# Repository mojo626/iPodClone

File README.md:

# iPodClone

This is a clone of an iPod video based on the Allwinner V3s processor

Features include:
- Allwinner V3s processor
- 1.54" TFT LCD
- ESP32 for WiFi and Bluetooth
- STGL5000 for wired headphone output
- 2500mAh battery
- microSD for music storage and filesystem
- NAND flash for boot

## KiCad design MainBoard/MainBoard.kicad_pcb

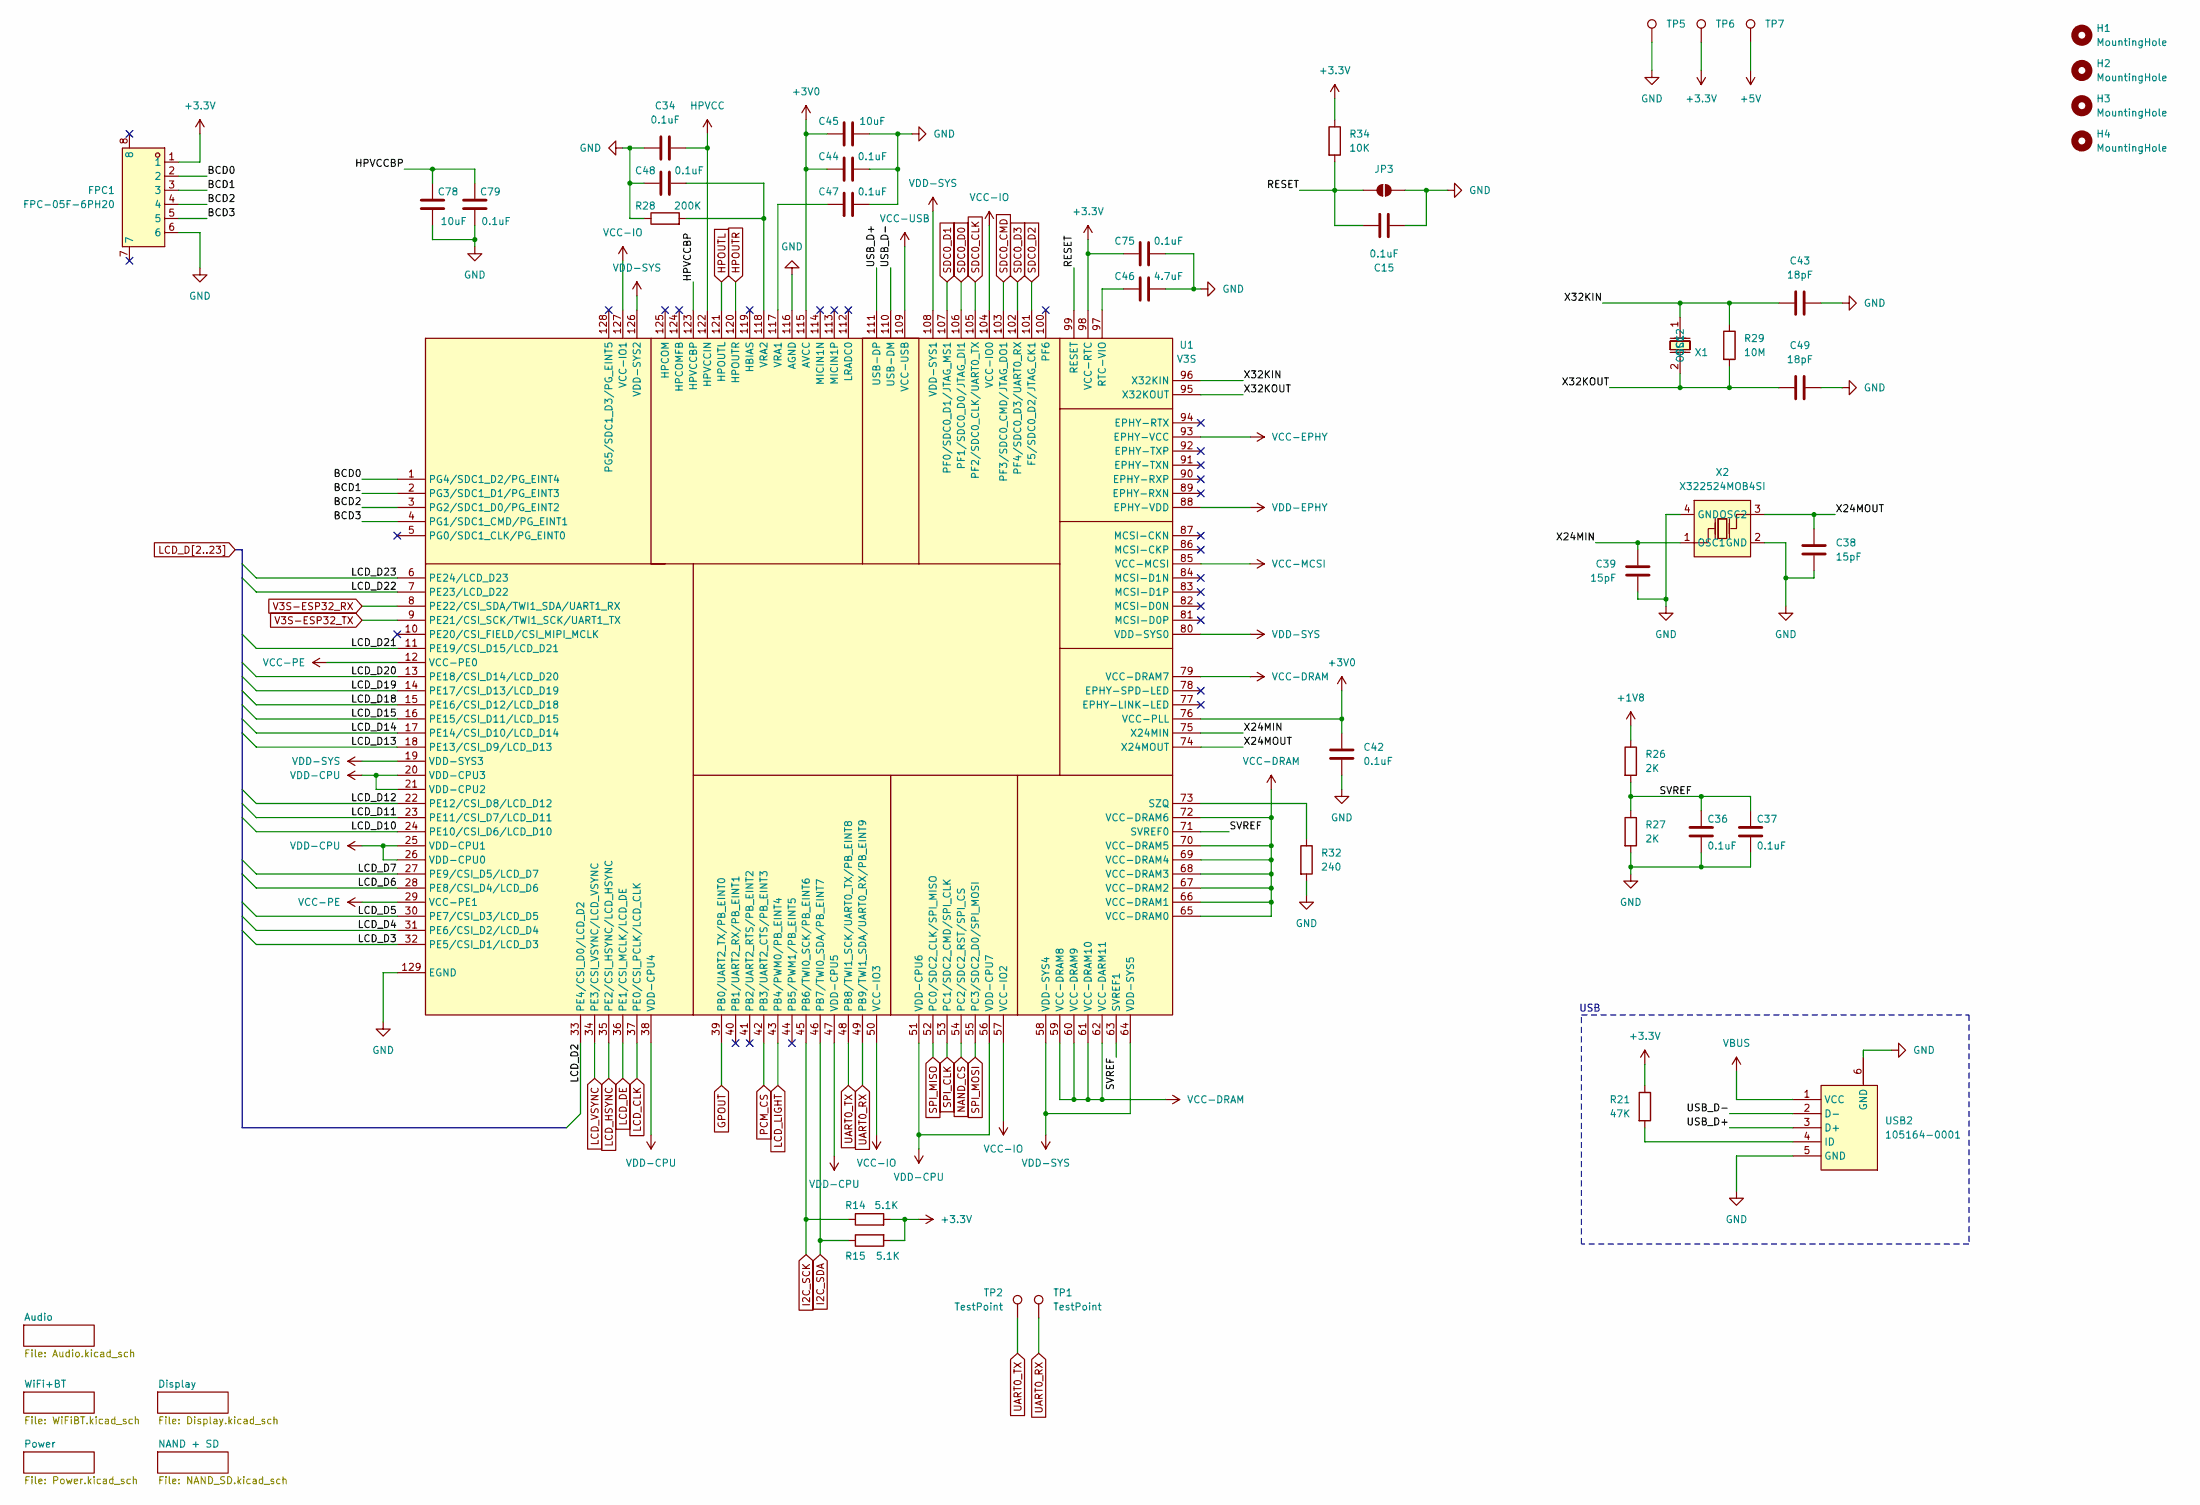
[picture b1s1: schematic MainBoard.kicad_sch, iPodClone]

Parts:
C15, C34, C36, C37, C42, C44, C47, C48, C75, C79: 0.1uF; C_0402_1005Metric
C38, C39: 15pF; C_0402_1005Metric
C43, C49: 18pF; C_0402_1005Metric
C45, C78: 10uF; C_0603_1608Metric
C46: 4.7uF; C_0402_1005Metric
FPC1: FPC-05F-6PH20; FPC-SMD_6P-P0.50_XUNPU_FPC-05F-6PH20; LCSC Part C2856796
H1, H2, H3, H4: MountingHole; MountingHole_2.2mm_M2
JP3: SolderJumper_2_Open; SolderJumper-2_P1.3mm_Open_Pad1.0x1.5mm
R14, R15: 5.1K; R_0402_1005Metric
R21: 47K; R_0402_1005Metric
R26, R27: 2K; R_0402_1005Metric
R28: 200K; R_0402_1005Metric
R29: 10M; R_0402_1005Metric
R32: 240; R_0402_1005Metric
R34: 10K; R_0402_1005Metric
TP1, TP2, TP5, TP6, TP7: TestPoint; TestPoint_Pad_1.5x1.5mm
U1: V3S; LQFP-128_L14.0-W14.0-P0.40-LS16.0-BL-EP5.0; LCSC Part C2687449
USB2: 105164-0001; MICRO-USB-SMD_5P-P0.65-H-F_105164-0001; LCSC Part C234179
X1: FC-12M32.768KHZ7PF20PPM; FC-12M_L2.0-W1.2; LCSC Part C99009
X2: X322524MOB4SI; CRYSTAL-SMD_4P-L3.2-W2.5-BL; LCSC Part C70590

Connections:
+1V2: U1.19 (VDD-SYS3), U1.20 (VDD-CPU3), U1.21 (VDD-CPU2), U1.25 (VDD-CPU1), U1.26 (VDD-CPU0), U1.38 (VDD-CPU4), U1.47 (VDD-CPU5), U1.51 (VDD-CPU6), U1.56 (VDD-CPU7), U1.58 (VDD-SYS4), U1.64 (VDD-SYS5), U1.80 (VDD-SYS0), U1.88 (EPHY-VDD), U1.108 (VDD-SYS1), U1.126 (VDD-SYS2); also elsewhere on the board
+1V8: R26.1, U1.59 (VCC-DRAM8), U1.60 (VCC-DRAM9), U1.61 (VCC-DRAM10), U1.62 (VCC-DARM11), U1.65 (VCC-DRAM0), U1.66 (VCC-DRAM1), U1.67 (VCC-DRAM2), U1.68 (VCC-DRAM3), U1.69 (VCC-DRAM4), U1.70 (VCC-DRAM5), U1.72 (VCC-DRAM6), U1.79 (VCC-DRAM7); also elsewhere on the board
+3.3V: C34.1, C75.2, FPC1.1, R14.2, R15.2, R21.1, R34.1, TP6.1, U1.12 (VCC-PE0), U1.29 (VCC-PE1), U1.50 (VCC-IO3), U1.57 (VCC-IO2), U1.85 (VCC-MCSI), U1.93 (EPHY-VCC), U1.98 (VCC-RTC), U1.104 (VCC-IO0), U1.109 (VCC-USB), U1.122 (HPVCCIN), U1.127 (VCC-IO1); also elsewhere on the board
+3V0: C42.1, C44.2, C45.2, U1.76 (VCC-PLL), U1.115 (AVCC); also elsewhere on the board
+5V: TP7.1; also elsewhere on the board
/BCD0: FPC1.2, U1.1 (PG4/SDC1_D2/PG_EINT4)
/BCD1: FPC1.3, U1.2 (PG3/SDC1_D1/PG_EINT3)
/BCD2: FPC1.4, U1.3 (PG2/SDC1_D0/PG_EINT2)
/BCD3: FPC1.5, U1.4 (PG1/SDC1_CMD/PG_EINT1)
/HPVCCBP: C78.2, C79.2, U1.123 (HPVCCBP)
/RESET: C15.1, JP3.2 (B), R34.2, U1.99 (RESET)
/SVREF: C36.1, C37.1, R26.2, R27.1, U1.63 (SVREF1), U1.71 (SVREF0)
/USB_D+: U1.111 (USB-DP), USB2.3 (D+)
/USB_D-: U1.110 (USB-DM), USB2.2 (D-)
/X24MIN: C39.1, U1.75 (X24MIN), X2.1 (OSC1)
/X24MOUT: C38.1, U1.74 (X24MOUT), X2.3 (OSC2)
/X32KIN: C43.1, R29.1, U1.96 (X32KIN), X1.1 (OSC1)
/X32KOUT: C49.1, R29.2, U1.95 (X32KOUT), X1.2 (OSC2)
GND: C15.2, C34.2, C36.2, C37.2, C38.2, C39.2, C42.2, C43.2, C44.1, C45.1, C46.1, C47.1, C48.2, C49.2, C75.1, C78.1, C79.1, FPC1.6, JP3.1 (A), R27.2, R28.1, R32.2, TP5.1, U1.116 (AGND), U1.129 (EGND), USB2.5 (GND), USB2.6 (GND), X2.2 (GND), X2.4 (GND); also elsewhere on the board
GPOUT: U1.39 (PB0/UART2_TX/PB_EINT0); also elsewhere on the board
HPOUTL: U1.121 (HPOUTL); also elsewhere on the board
HPOUTR: U1.120 (HPOUTR); also elsewhere on the board
I2C_SCK: R14.1, U1.45 (PB6/TWI0_SCK/PB_EINT6); also elsewhere on the board
I2C_SDA: R15.1, U1.46 (PB7/TWI0_SDA/PB_EINT7); also elsewhere on the board
LCD_CLK: U1.37 (PE0/CSI_PCLK/LCD_CLK); also elsewhere on the board
LCD_D2: U1.33 (PE4/CSI_D0/LCD_D2); also elsewhere on the board
LCD_D3: U1.32 (PE5/CSI_D1/LCD_D3); also elsewhere on the board
LCD_D4: U1.31 (PE6/CSI_D2/LCD_D4); also elsewhere on the board
LCD_D5: U1.30 (PE7/CSI_D3/LCD_D5); also elsewhere on the board
LCD_D6: U1.28 (PE8/CSI_D4/LCD_D6); also elsewhere on the board
LCD_D7: U1.27 (PE9/CSI_D5/LCD_D7); also elsewhere on the board
LCD_D10: U1.24 (PE10/CSI_D6/LCD_D10); also elsewhere on the board
LCD_D11: U1.23 (PE11/CSI_D7/LCD_D11); also elsewhere on the board
LCD_D12: U1.22 (PE12/CSI_D8/LCD_D12); also elsewhere on the board
LCD_D13: U1.18 (PE13/CSI_D9/LCD_D13); also elsewhere on the board
LCD_D14: U1.17 (PE14/CSI_D10/LCD_D14); also elsewhere on the board
LCD_D15: U1.16 (PE15/CSI_D11/LCD_D15); also elsewhere on the board
LCD_D18: U1.15 (PE16/CSI_D12/LCD_D18); also elsewhere on the board
LCD_D19: U1.14 (PE17/CSI_D13/LCD_D19); also elsewhere on the board
LCD_D20: U1.13 (PE18/CSI_D14/LCD_D20); also elsewhere on the board
LCD_D21: U1.11 (PE19/CSI_D15/LCD_D21); also elsewhere on the board
LCD_D22: U1.7 (PE23/LCD_D22); also elsewhere on the board
LCD_D23: U1.6 (PE24/LCD_D23); also elsewhere on the board
LCD_DE: U1.36 (PE1/CSI_MCLK/LCD_DE); also elsewhere on the board
LCD_HSYNC: U1.35 (PE2/CSI_HSYNC/LCD_HSYNC); also elsewhere on the board
LCD_LIGHT: U1.43 (PB4/PWM0/PB_EINT4); also elsewhere on the board
LCD_VSYNC: U1.34 (PE3/CSI_VSYNC/LCD_VSYNC); also elsewhere on the board
NAND_CS: U1.54 (PC2/SDC2_RST/SPI_CS); also elsewhere on the board
unnamed: C46.2, U1.97 (RTC-VIO)
unnamed: R32.1, U1.73 (SZQ)
unnamed: C47.2, U1.117 (VRA1)
unnamed: C48.1, R28.2, U1.118 (VRA2)
unnamed: R21.2, USB2.4 (ID)
PCM_CS: U1.42 (PB3/UART2_CTS/PB_EINT3); also elsewhere on the board
SDC0_CLK: U1.105 (PF2/SDC0_CLK/UART0_TX); also elsewhere on the board
SDC0_CMD: U1.103 (PF3/SDC0_CMD/JTAG_DO1); also elsewhere on the board
SDC0_D0: U1.106 (PF1/SDC0_D0/JTAG_DI1); also elsewhere on the board
SDC0_D1: U1.107 (PF0/SDC0_D1/JTAG_MS1); also elsewhere on the board
SDC0_D2: U1.101 (F5/SDC0_D2/JTAG_CK1); also elsewhere on the board
SDC0_D3: U1.102 (PF4/SDC0_D3/UART0_RX); also elsewhere on the board
SPI_CLK: U1.53 (PC1/SDC2_CMD/SPI_CLK); also elsewhere on the board
SPI_MISO: U1.52 (PC0/SDC2_CLK/SPI_MISO); also elsewhere on the board
SPI_MOSI: U1.55 (PC3/SDC2_D0/SPI_MOSI); also elsewhere on the board
UART0_RX: TP1.1, U1.49 (PB9/TWI1_SDA/UART0_RX/PB_EINT9)
UART0_TX: TP2.1, U1.48 (PB8/TWI1_SCK/UART0_TX/PB_EINT8)
V3S-ESP32_RX: U1.8 (PE22/CSI_SDA/TWI1_SDA/UART1_RX); also elsewhere on the board
V3S-ESP32_TX: U1.9 (PE21/CSI_SCK/TWI1_SCK/UART1_TX); also elsewhere on the board
VBUS: USB2.1 (VCC); also elsewhere on the board

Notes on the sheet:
USB

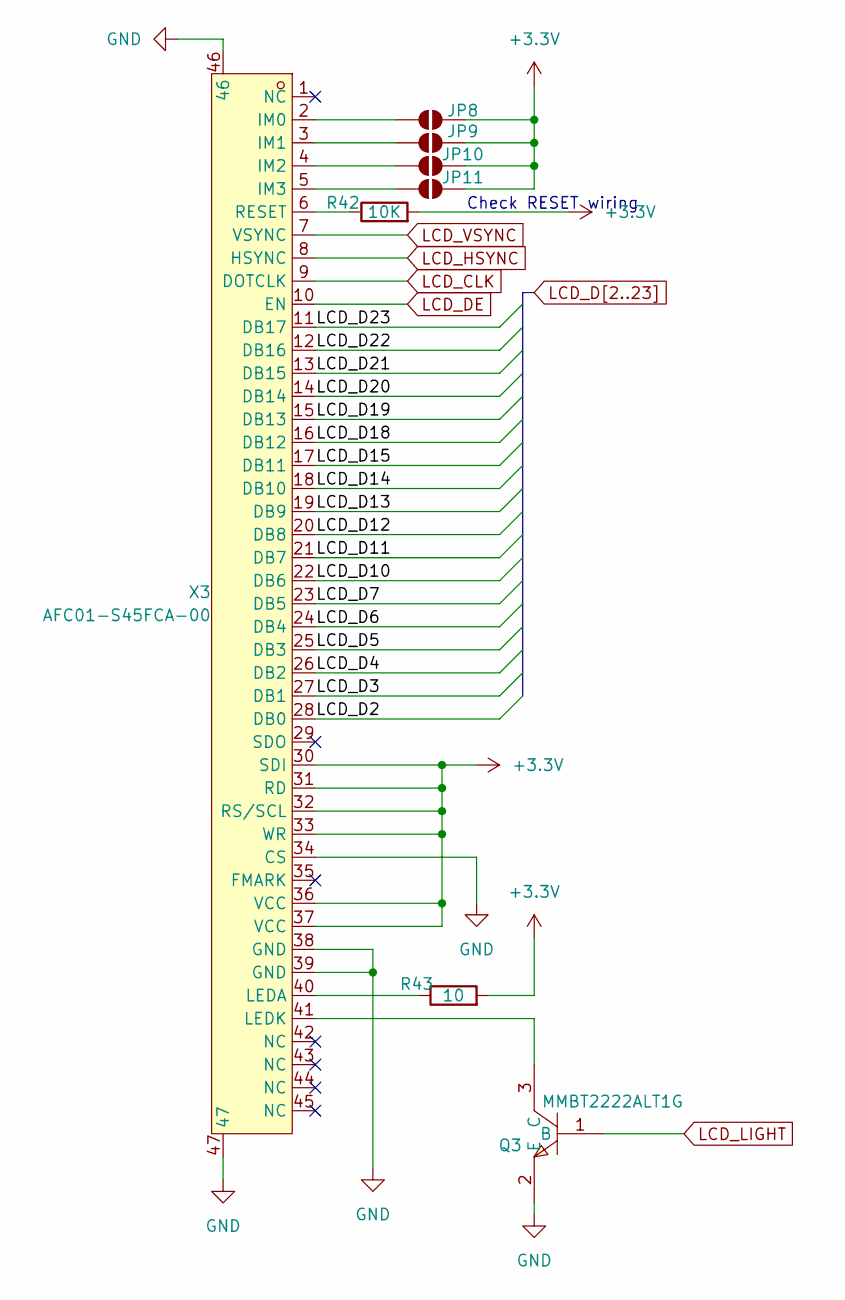
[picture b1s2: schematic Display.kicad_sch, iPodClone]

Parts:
JP8, JP9, JP10, JP11: SolderJumper_2_Open; SolderJumper-2_P1.3mm_Open_TrianglePad1.0x1.5mm
Q3: MMBT2222ALT1G; SOT-23-3_L2.9-W1.3-P1.90-LS2.4-BR; LCSC Part C82460
R42: 10K; R_0402_1005Metric
R43: 10; R_0402_1005Metric
X3: AFC01-S45FCA-00; FPC-SMD_AFC01-S45FCA-00; LCSC Part C262675

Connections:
+3.3V: JP8.2 (B), JP9.2 (B), JP10.2 (B), JP11.2 (B), R42.2, R43.2, X3.30 (SDI), X3.31 (RD), X3.32 (RS/SCL), X3.33 (WR), X3.36 (VCC), X3.37 (VCC); also elsewhere on the board
GND: Q3.2 (E), X3.34 (CS), X3.38 (GND), X3.39 (GND), X3.46, X3.47; also elsewhere on the board
LCD_CLK: X3.9 (DOTCLK); also elsewhere on the board
LCD_D2: X3.28 (DB0); also elsewhere on the board
LCD_D3: X3.27 (DB1); also elsewhere on the board
LCD_D4: X3.26 (DB2); also elsewhere on the board
LCD_D5: X3.25 (DB3); also elsewhere on the board
LCD_D6: X3.24 (DB4); also elsewhere on the board
LCD_D7: X3.23 (DB5); also elsewhere on the board
LCD_D10: X3.22 (DB6); also elsewhere on the board
LCD_D11: X3.21 (DB7); also elsewhere on the board
LCD_D12: X3.20 (DB8); also elsewhere on the board
LCD_D13: X3.19 (DB9); also elsewhere on the board
LCD_D14: X3.18 (DB10); also elsewhere on the board
LCD_D15: X3.17 (DB11); also elsewhere on the board
LCD_D18: X3.16 (DB12); also elsewhere on the board
LCD_D19: X3.15 (DB13); also elsewhere on the board
LCD_D20: X3.14 (DB14); also elsewhere on the board
LCD_D21: X3.13 (DB15); also elsewhere on the board
LCD_D22: X3.12 (DB16); also elsewhere on the board
LCD_D23: X3.11 (DB17); also elsewhere on the board
LCD_DE: X3.10 (EN); also elsewhere on the board
LCD_HSYNC: X3.8 (HSYNC); also elsewhere on the board
LCD_LIGHT: Q3.1 (B); also elsewhere on the board
LCD_VSYNC: X3.7 (VSYNC); also elsewhere on the board
unnamed: JP8.1 (A), X3.2 (IM0)
unnamed: JP9.1 (A), X3.3 (IM1)
unnamed: JP10.1 (A), X3.4 (IM2)
unnamed: JP11.1 (A), X3.5 (IM3)
unnamed: Q3.3 (C), X3.41 (LEDK)
unnamed: R43.1, X3.40 (LEDA)
unnamed: R42.1, X3.6 (RESET)

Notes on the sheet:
Check RESET wiring

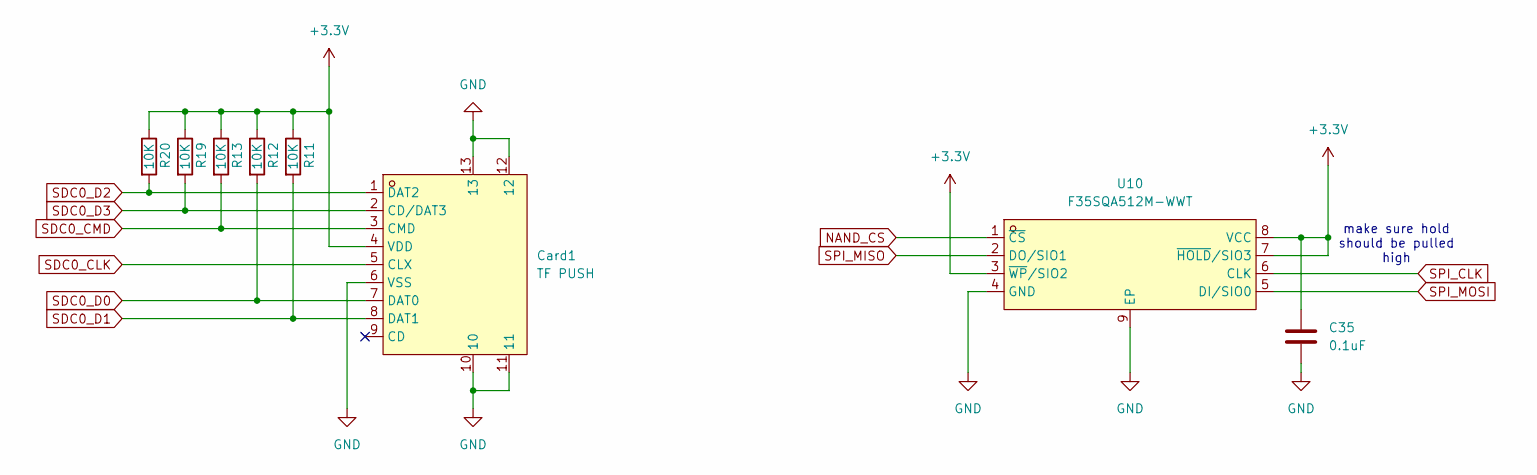
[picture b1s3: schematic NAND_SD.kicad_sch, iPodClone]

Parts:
C35: 0.1uF; C_0402_1005Metric
Card1: TF PUSH; TF-SMD_TF-PUSH; LCSC Part C393941
R11, R12, R13, R19, R20: 10K; R_0402_1005Metric
U10: F35SQA512M-WWT; WSON-8_L8.0-W6.0-P1.27-BL-EP-1; LCSC Part C5126826

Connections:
+3.3V: C35.1, Card1.4 (VDD), R11.1, R12.1, R13.1, R19.1, R20.1, U10.3 (~WP/SIO2), U10.7 (~HOLD/SIO3), U10.8 (VCC); also elsewhere on the board
GND: C35.2, Card1.6 (VSS), Card1.10, Card1.11, Card1.12, Card1.13, U10.4 (GND), U10.9 (EP); also elsewhere on the board
NAND_CS: U10.1 (~CS); also elsewhere on the board
SDC0_CLK: Card1.5 (CLX); also elsewhere on the board
SDC0_CMD: Card1.3 (CMD), R13.2; also elsewhere on the board
SDC0_D0: Card1.7 (DAT0), R12.2; also elsewhere on the board
SDC0_D1: Card1.8 (DAT1), R11.2; also elsewhere on the board
SDC0_D2: Card1.1 (DAT2), R20.2; also elsewhere on the board
SDC0_D3: Card1.2 (CD/DAT3), R19.2; also elsewhere on the board
SPI_CLK: U10.6 (CLK); also elsewhere on the board
SPI_MISO: U10.2 (DO/SIO1); also elsewhere on the board
SPI_MOSI: U10.5 (DI/SIO0); also elsewhere on the board

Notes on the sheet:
make sure hold should be pulled high

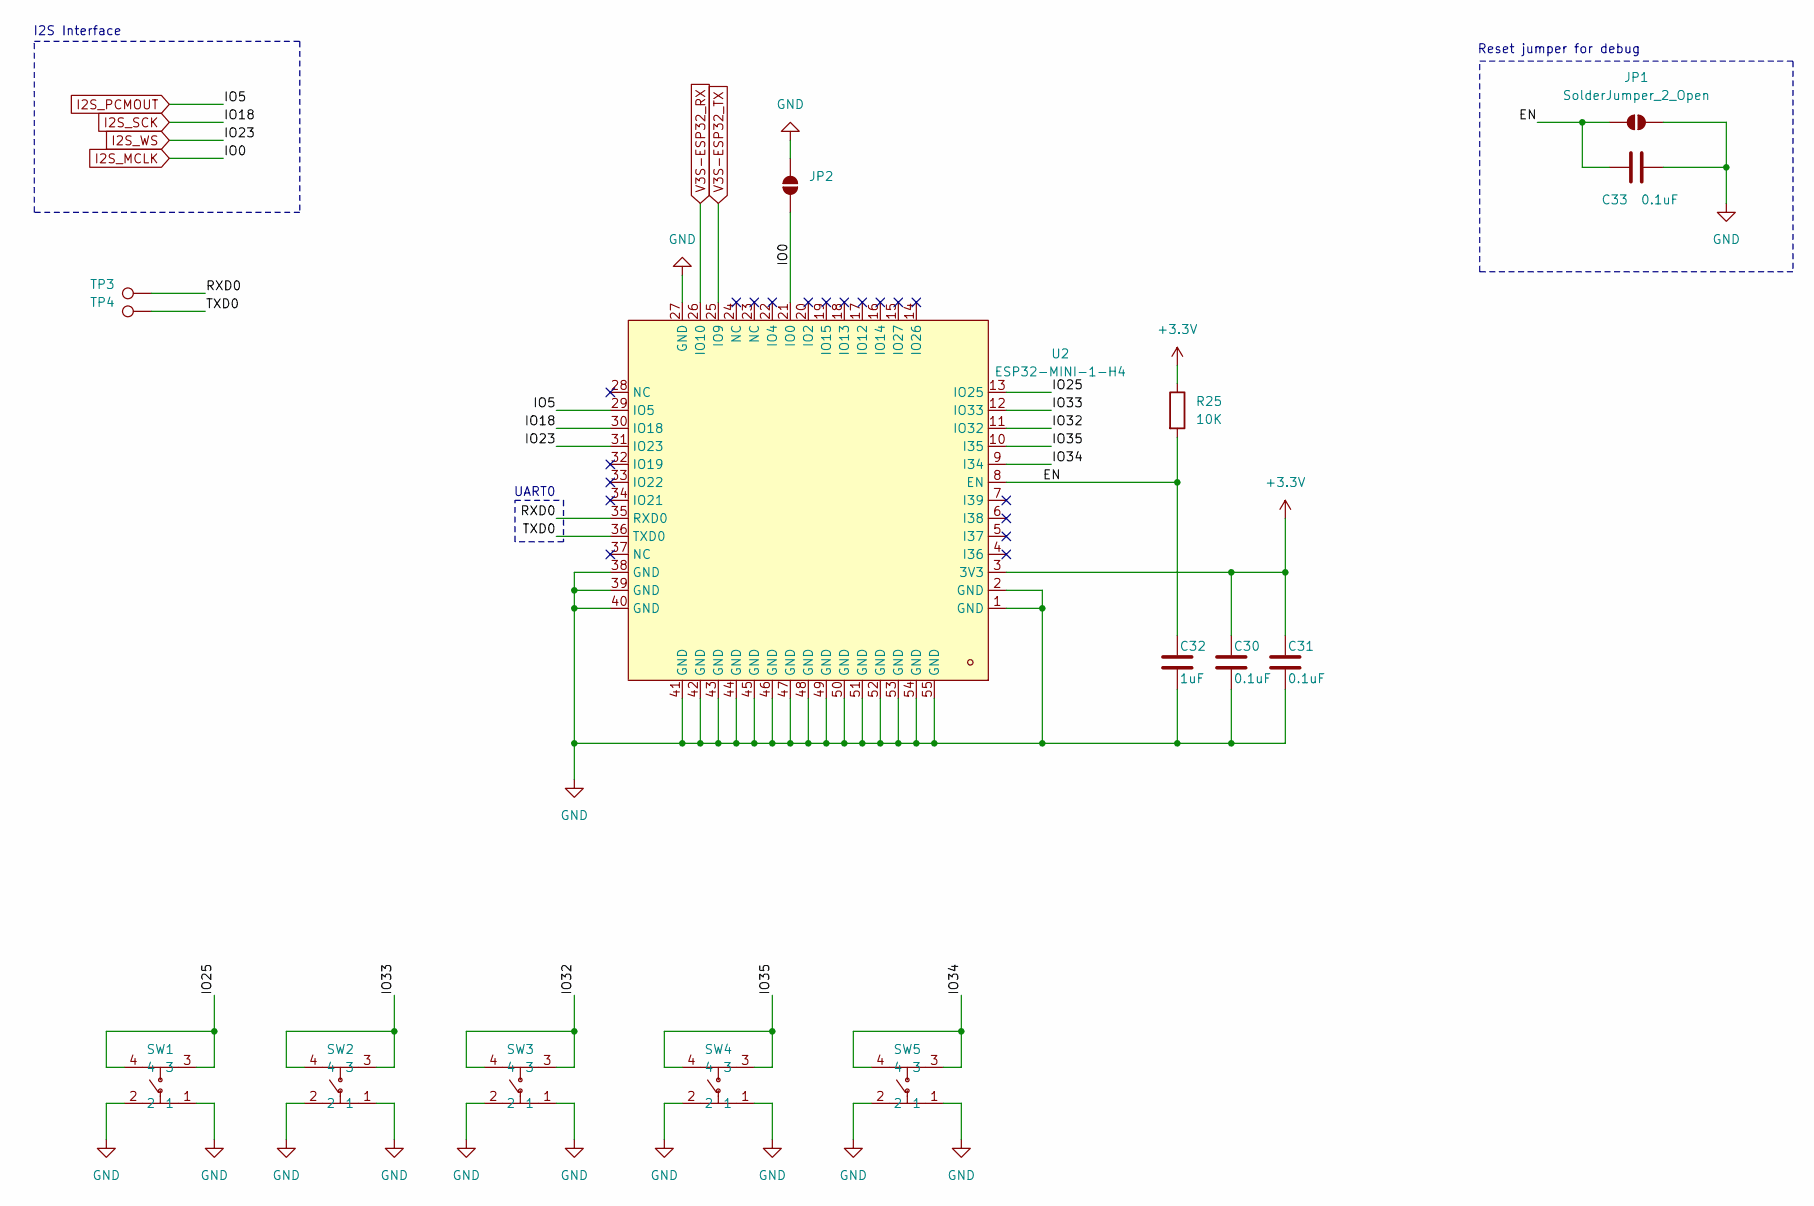
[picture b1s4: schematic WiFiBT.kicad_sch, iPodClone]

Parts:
C30, C31, C33: 0.1uF; C_0402_1005Metric
C32: 1uF; C_0402_1005Metric
JP1, JP2: SolderJumper_2_Open; SolderJumper-2_P1.3mm_Open_Pad1.0x1.5mm
R25: 10K; R_0402_1005Metric
SW1, SW2, SW3, SW4, SW5: TS3735A 250GF 030; SW-SMD_4P-L3.7-W3.7-P2.70-LS3.7; LCSC Part C2906282
TP3, TP4: TestPoint; TestPoint_Pad_1.5x1.5mm
U2: ESP32-MINI-1-H4; WIFI-SMD_ESP32-MINI-1; LCSC Part C3013933

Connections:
+3.3V: C30.1, C31.1, R25.1, U2.3 (3V3); also elsewhere on the board
/WiFi+BT/EN: C32.1, C33.1, JP1.1 (A), R25.2, U2.8 (EN)
/WiFi+BT/IO25: SW1.3, SW1.4, U2.13 (IO25)
/WiFi+BT/IO32: SW3.3, SW3.4, U2.11 (IO32)
/WiFi+BT/IO33: SW2.3, SW2.4, U2.12 (IO33)
/WiFi+BT/IO34: SW5.3, SW5.4, U2.9 (I34)
/WiFi+BT/IO35: SW4.3, SW4.4, U2.10 (I35)
/WiFi+BT/RXD0: TP3.1, U2.35 (RXD0)
/WiFi+BT/TXD0: TP4.1, U2.36 (TXD0)
GND: C30.2, C31.2, C32.2, C33.2, JP1.2 (B), JP2.2 (B), SW1.1, SW1.2, SW2.1, SW2.2, SW3.1, SW3.2, SW4.1, SW4.2, SW5.1, SW5.2, U2.1 (GND), U2.2 (GND), U2.27 (GND), U2.38 (GND), U2.39 (GND), U2.40 (GND), U2.41 (GND), U2.42 (GND), U2.43 (GND), U2.44 (GND), U2.45 (GND), U2.46 (GND), U2.47 (GND), U2.48 (GND), U2.49 (GND), U2.50 (GND), U2.51 (GND), U2.52 (GND), U2.53 (GND), U2.54 (GND), U2.55 (GND); also elsewhere on the board
I2S_MCLK: JP2.1 (A), U2.21 (IO0); also elsewhere on the board
I2S_PCMOUT: U2.29 (IO5); also elsewhere on the board
I2S_SCK: U2.30 (IO18); also elsewhere on the board
I2S_WS: U2.31 (IO23); also elsewhere on the board
V3S-ESP32_RX: U2.26 (IO10); also elsewhere on the board
V3S-ESP32_TX: U2.25 (IO9); also elsewhere on the board

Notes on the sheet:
UART0
I2S Interface
Reset jumper for debug

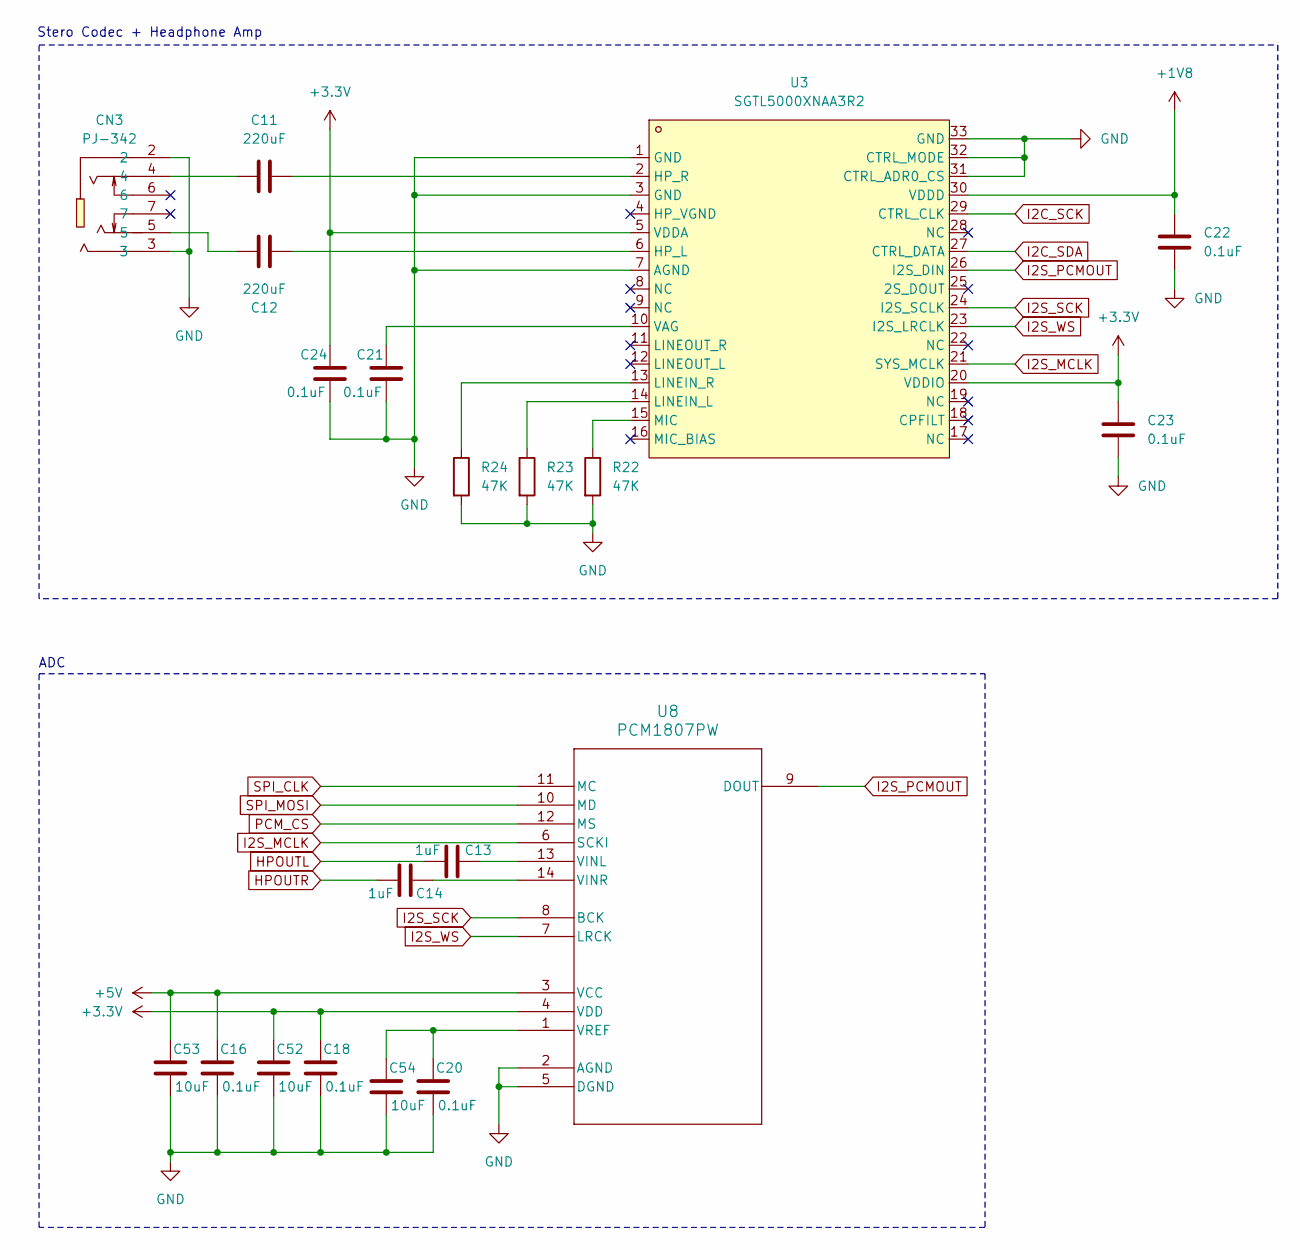
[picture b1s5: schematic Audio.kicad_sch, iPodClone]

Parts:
C11, C12: 220uF; C_1206_3216Metric
C13, C14: 1uF; C_0402_1005Metric
C16, C18, C20, C21, C22, C23, C24: 0.1uF; C_0402_1005Metric
C52, C53, C54: 10uF; C_0603_1608Metric
CN3: PJ-342; AUDIO-SMD_PJ-342; LCSC Part C668606
R22, R23, R24: 47K; R_0402_1005Metric
U3: SGTL5000XNAA3R2; QFN-32_L5.0-W5.0-P0.50-BL-EP3.4; LCSC Part C4991065
U8: PCM1807PW; PW14

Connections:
+1V8: C22.1, U3.30 (VDDD); also elsewhere on the board
+3.3V: C18.1, C23.1, C24.1, C52.1, U3.5 (VDDA), U3.20 (VDDIO), U8.4 (VDD); also elsewhere on the board
+5V: C16.1, C53.1, U8.3 (VCC); also elsewhere on the board
GND: C16.2, C18.2, C20.2, C21.2, C22.2, C23.2, C24.2, C52.2, C53.2, C54.2, CN3.2, CN3.3, R22.2, R23.2, R24.2, U3.1 (GND), U3.3 (GND), U3.7 (AGND), U3.31 (CTRL_ADR0_CS), U3.32 (CTRL_MODE), U3.33 (GND), U8.2 (AGND), U8.5 (DGND); also elsewhere on the board
HPOUTL: C13.1; also elsewhere on the board
HPOUTR: C14.1; also elsewhere on the board
I2C_SCK: U3.29 (CTRL_CLK); also elsewhere on the board
I2C_SDA: U3.27 (CTRL_DATA); also elsewhere on the board
I2S_MCLK: U3.21 (SYS_MCLK), U8.6 (SCKI); also elsewhere on the board
I2S_PCMOUT: U3.26 (I2S_DIN), U8.9 (DOUT); also elsewhere on the board
I2S_SCK: U3.24 (I2S_SCLK), U8.8 (BCK); also elsewhere on the board
I2S_WS: U3.23 (I2S_LRCLK), U8.7 (LRCK); also elsewhere on the board
unnamed: C11.1, CN3.4
unnamed: C12.1, CN3.5
unnamed: C12.2, U3.6 (HP_L)
unnamed: C11.2, U3.2 (HP_R)
unnamed: R23.1, U3.14 (LINEIN_L)
unnamed: R24.1, U3.13 (LINEIN_R)
unnamed: R22.1, U3.15 (MIC)
unnamed: C21.1, U3.10 (VAG)
unnamed: C13.2, U8.13 (VINL)
unnamed: C14.2, U8.14 (VINR)
unnamed: C20.1, C54.1, U8.1 (VREF)
PCM_CS: U8.12 (MS); also elsewhere on the board
SPI_CLK: U8.11 (MC); also elsewhere on the board
SPI_MOSI: U8.10 (MD); also elsewhere on the board

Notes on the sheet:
ADC
Stero Codec + Headphone Amp

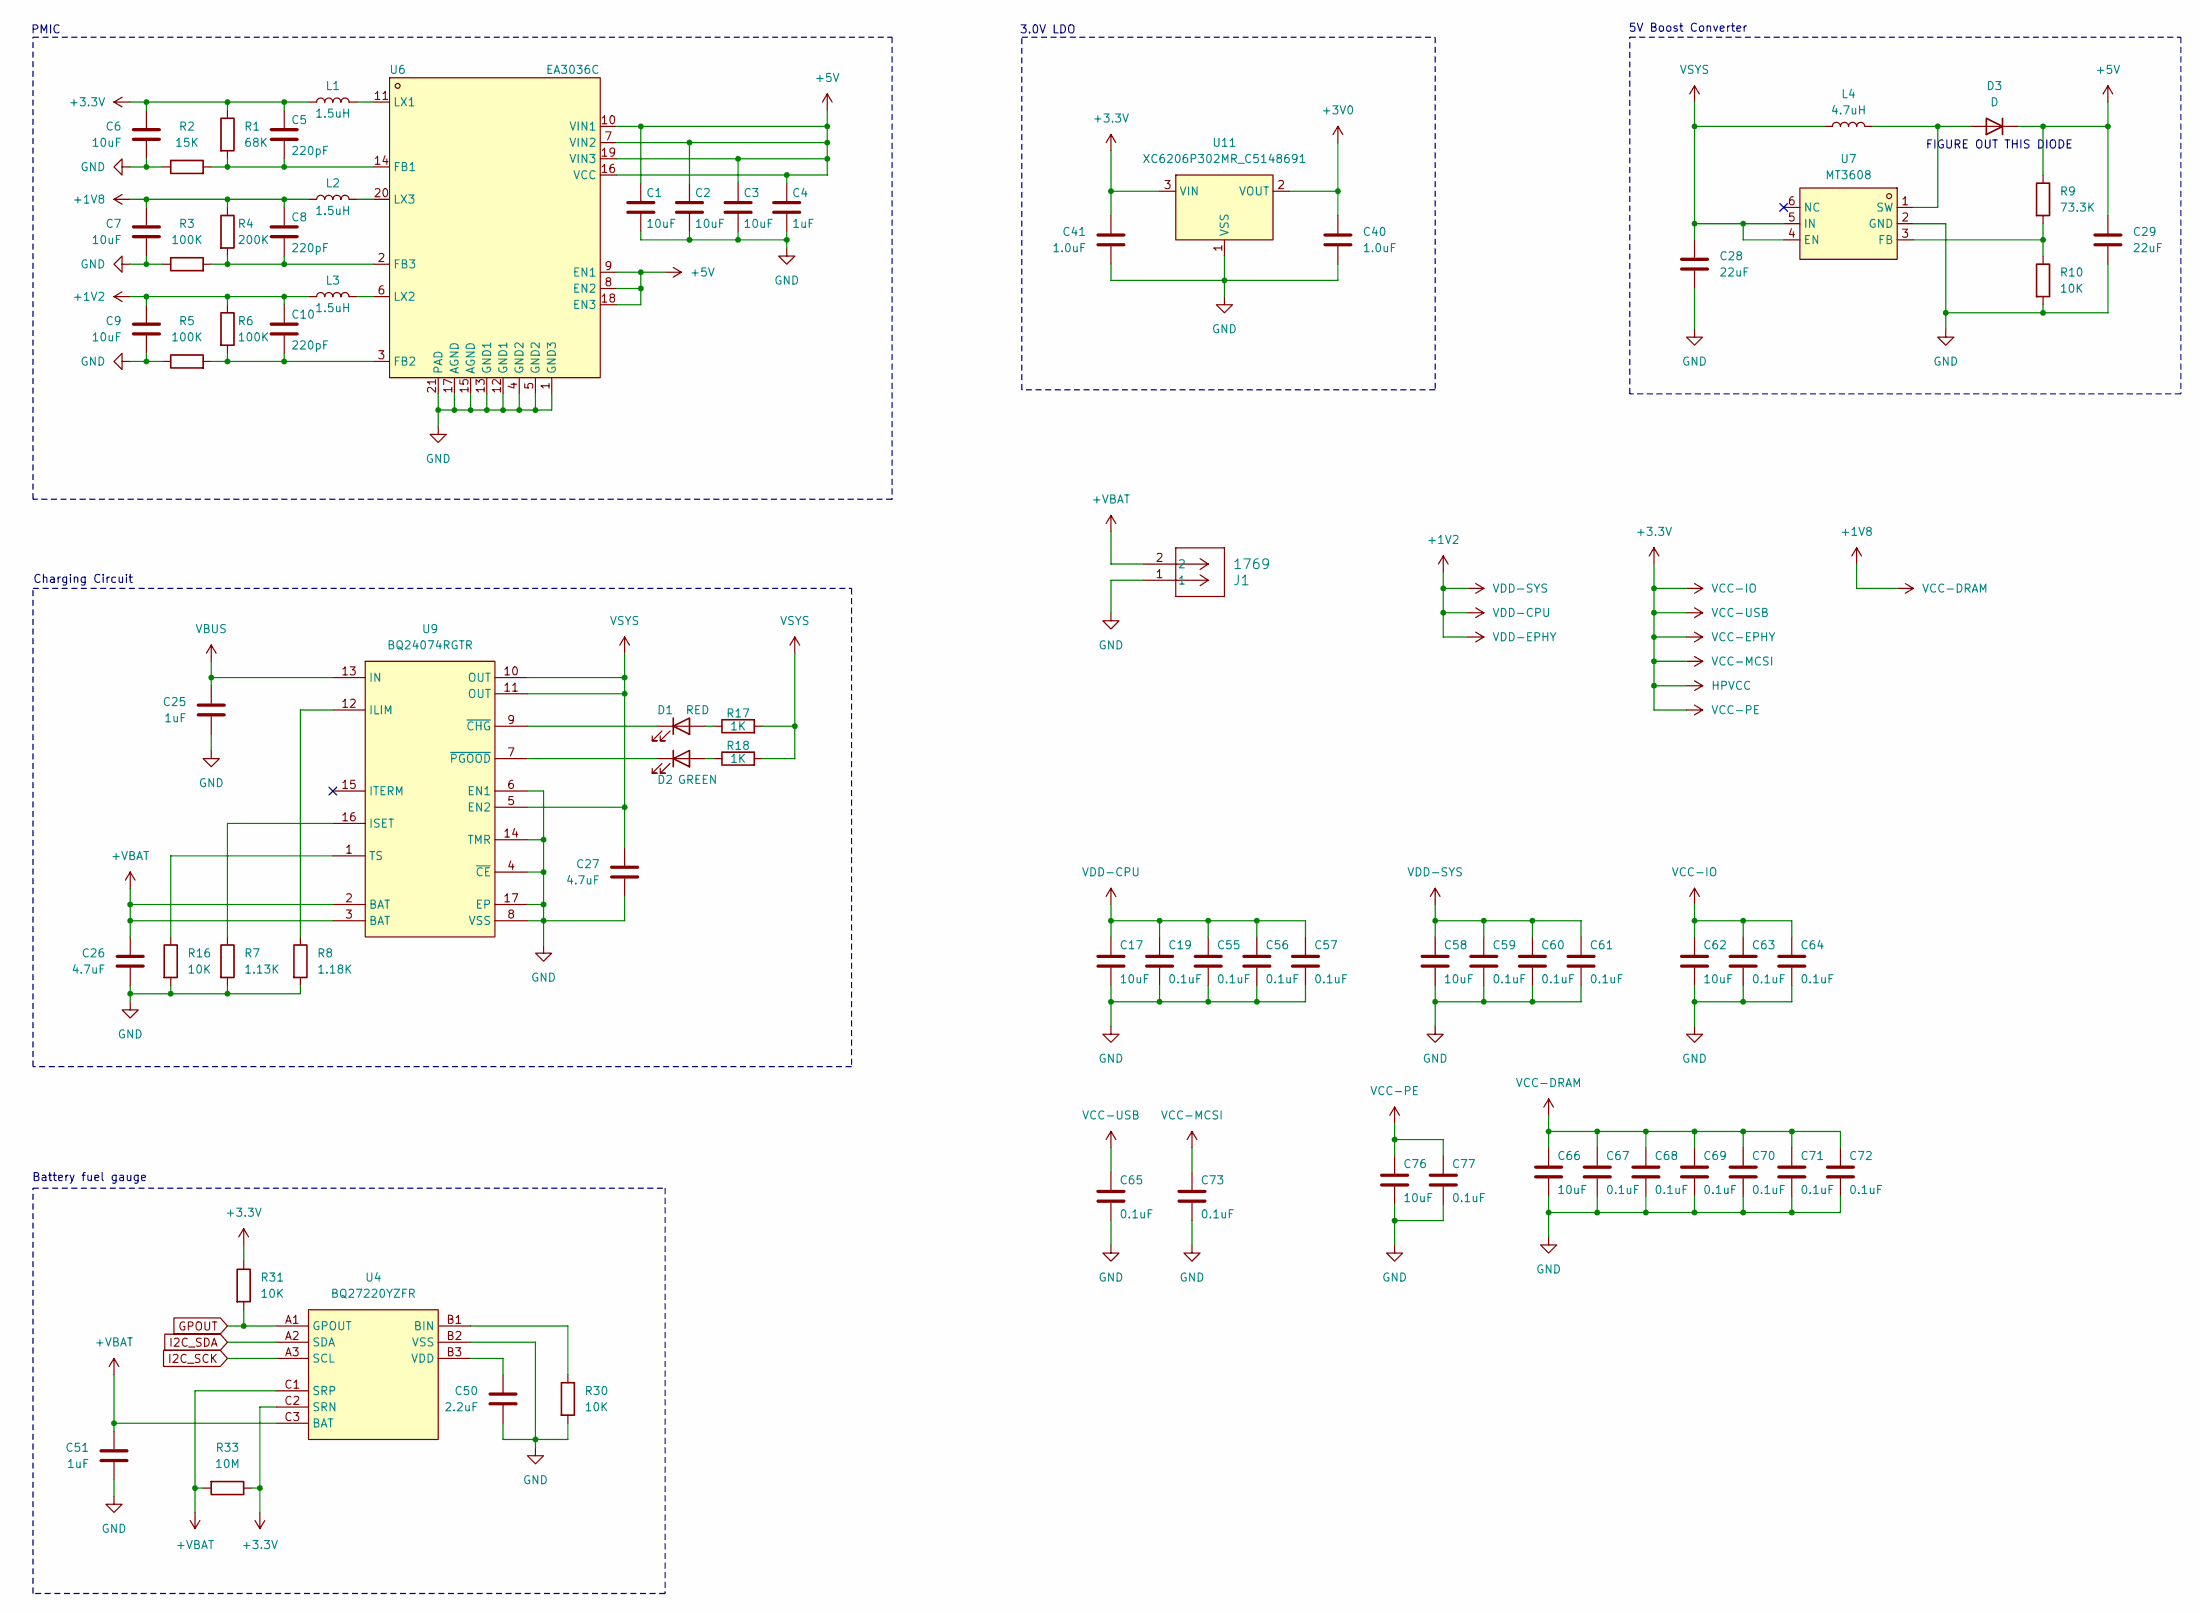
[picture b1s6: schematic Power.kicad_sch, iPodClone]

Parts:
C1, C2, C3, C6, C7, C9, C17, C58, C62, C66, C76: 10uF; C_0603_1608Metric
C4, C25, C51: 1uF; C_0402_1005Metric
C5, C8, C10: 220pF; C_0402_1005Metric
C19, C55, C56, C57, C59, C60, C61, C63, C64, C65, C67, C68, C69, C70, C71, C72, C73, C77: 0.1uF; C_0402_1005Metric
C26, C27: 4.7uF; C_0402_1005Metric
C28, C29: 22uF; C_0603_1608Metric
C40, C41: 1.0uF; C_0402_1005Metric
C50: 2.2uF; C_0402_1005Metric
D1: RED; LED_0402_1005Metric
D2: GREEN; LED_0402_1005Metric
D3: D; D_0603_1608Metric
J1: 1769; CONN_1769_ADA
L1, L2, L3: 1.5uH; L_0402_1005Metric
L4: 4.7uH; L_0402_1005Metric
R1: 68K; R_0402_1005Metric
R2: 15K; R_0402_1005Metric
R3, R5, R6: 100K; R_0402_1005Metric
R4: 200K; R_0402_1005Metric
R7: 1.13K; R_0402_1005Metric
R8: 1.18K; R_0402_1005Metric
R9: 73.3K; R_0402_1005Metric
R10, R16, R30, R31: 10K; R_0402_1005Metric
R17, R18: 1K; R_0402_1005Metric
R33: 10M; R_0402_1005Metric
U4: BQ27220YZFR; DSBGA-9_L1.7-W1.6-R3-C3-P0.50-BL; LCSC Part C528617
U6: EA3036C; WQFN-20_L3.0-W3.0-P0.40-BL-EP; LCSC Part C570857
U7: MT3608; SOT-23-6_L2.9-W1.6-P0.95-LS2.8-BL; LCSC Part C84817
U9: BQ24074RGTR; QFN-16_L3.0-W3.0-P0.50-TL-EP1.7; LCSC Part C54313
U11: XC6206P302MR_C5148691; SOT-23-3_L3.0-W1.7-P0.95-LS2.9-BR; LCSC Part C5148691

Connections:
+1V2: C9.1, C10.1, C17.1, C19.1, C55.1, C56.1, C57.1, C58.1, C59.1, C60.1, C61.1, L3.1, R6.1; also elsewhere on the board
+1V8: C7.1, C8.1, C66.1, C67.1, C68.1, C69.1, C70.1, C71.1, C72.1, L2.1, R4.1; also elsewhere on the board
+3.3V: C5.1, C6.1, C41.1, C62.1, C63.1, C64.1, C65.1, C73.1, C76.1, C77.1, L1.1, R1.1, R31.1, R33.1, U4.C2 (SRN), U11.3 (VIN); also elsewhere on the board
+3V0: C40.1, U11.2 (VOUT); also elsewhere on the board
+5V: C1.1, C2.1, C3.1, C4.1, C29.1, D3.1 (K), R9.1, U6.7 (VIN2), U6.8 (EN2), U6.9 (EN1), U6.10 (VIN1), U6.16 (VCC), U6.18 (EN3), U6.19 (VIN3); also elsewhere on the board
+VBAT: C26.1, C51.1, J1.2, R33.2, U4.C1 (SRP), U4.C3 (BAT), U9.2 (BAT), U9.3 (BAT)
GND: C1.2, C2.2, C3.2, C4.2, C6.2, C7.2, C9.2, C17.2, C19.2, C25.2, C26.2, C27.2, C28.2, C29.2, C40.2, C41.2, C50.2, C51.2, C55.2, C56.2, C57.2, C58.2, C59.2, C60.2, C61.2, C62.2, C63.2, C64.2, C65.2, C66.2, C67.2, C68.2, C69.2, C70.2, C71.2, C72.2, C73.2, C76.2, C77.2, J1.1, R2.1, R3.1, R5.1, R7.2, R8.2, R10.2, R16.2, R30.2, U4.B2 (VSS), U6.1 (GND3), U6.4 (GND2), U6.5 (GND2), U6.12 (GND1), U6.13 (GND1), U6.15 (AGND), U6.17 (AGND), U6.21 (PAD), U7.2 (GND), U9.4 (~CE), U9.6 (EN1), U9.8 (VSS), U9.14 (TMR), U9.17 (EP), U11.1 (VSS); also elsewhere on the board
GPOUT: R31.2, U4.A1 (GPOUT); also elsewhere on the board
I2C_SCK: U4.A3 (SCL); also elsewhere on the board
I2C_SDA: U4.A2 (SDA); also elsewhere on the board
unnamed: D1.2 (A), R17.1
unnamed: D1.1 (K), U9.9 (~CHG)
unnamed: D2.2 (A), R18.1
unnamed: D2.1 (K), U9.7 (~PGOOD)
unnamed: D3.2 (A), L4.2, U7.1 (SW)
unnamed: R30.1, U4.B1 (BIN)
unnamed: C50.1, U4.B3 (VDD)
unnamed: C5.2, R1.2, R2.2, U6.14 (FB1)
unnamed: C10.2, R5.2, R6.2, U6.3 (FB2)
unnamed: C8.2, R3.2, R4.2, U6.2 (FB3)
unnamed: L1.2, U6.11 (LX1)
unnamed: L3.2, U6.6 (LX2)
unnamed: L2.2, U6.20 (LX3)
unnamed: R9.2, R10.1, U7.3 (FB)
unnamed: R8.1, U9.12 (ILIM)
unnamed: R7.1, U9.16 (ISET)
unnamed: R16.1, U9.1 (TS)
VBUS: C25.1, U9.13 (IN); also elsewhere on the board
VSYS: C27.1, C28.1, L4.1, R17.2, R18.2, U7.4 (EN), U7.5 (IN), U9.5 (EN2), U9.10 (OUT), U9.11 (OUT)

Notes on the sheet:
FIGURE OUT THIS DIODE
5V Boost Converter
Charging Circuit
PMIC
Battery fuel gauge
3.0V LDO
